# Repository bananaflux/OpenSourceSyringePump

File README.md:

# OpenSourceSyringePump

* Printed circuit board can be easily ordered from OSHPark: [Open Source Syringe Pump PCB](https://oshpark.com/shared_projects/VtseE2Ia)

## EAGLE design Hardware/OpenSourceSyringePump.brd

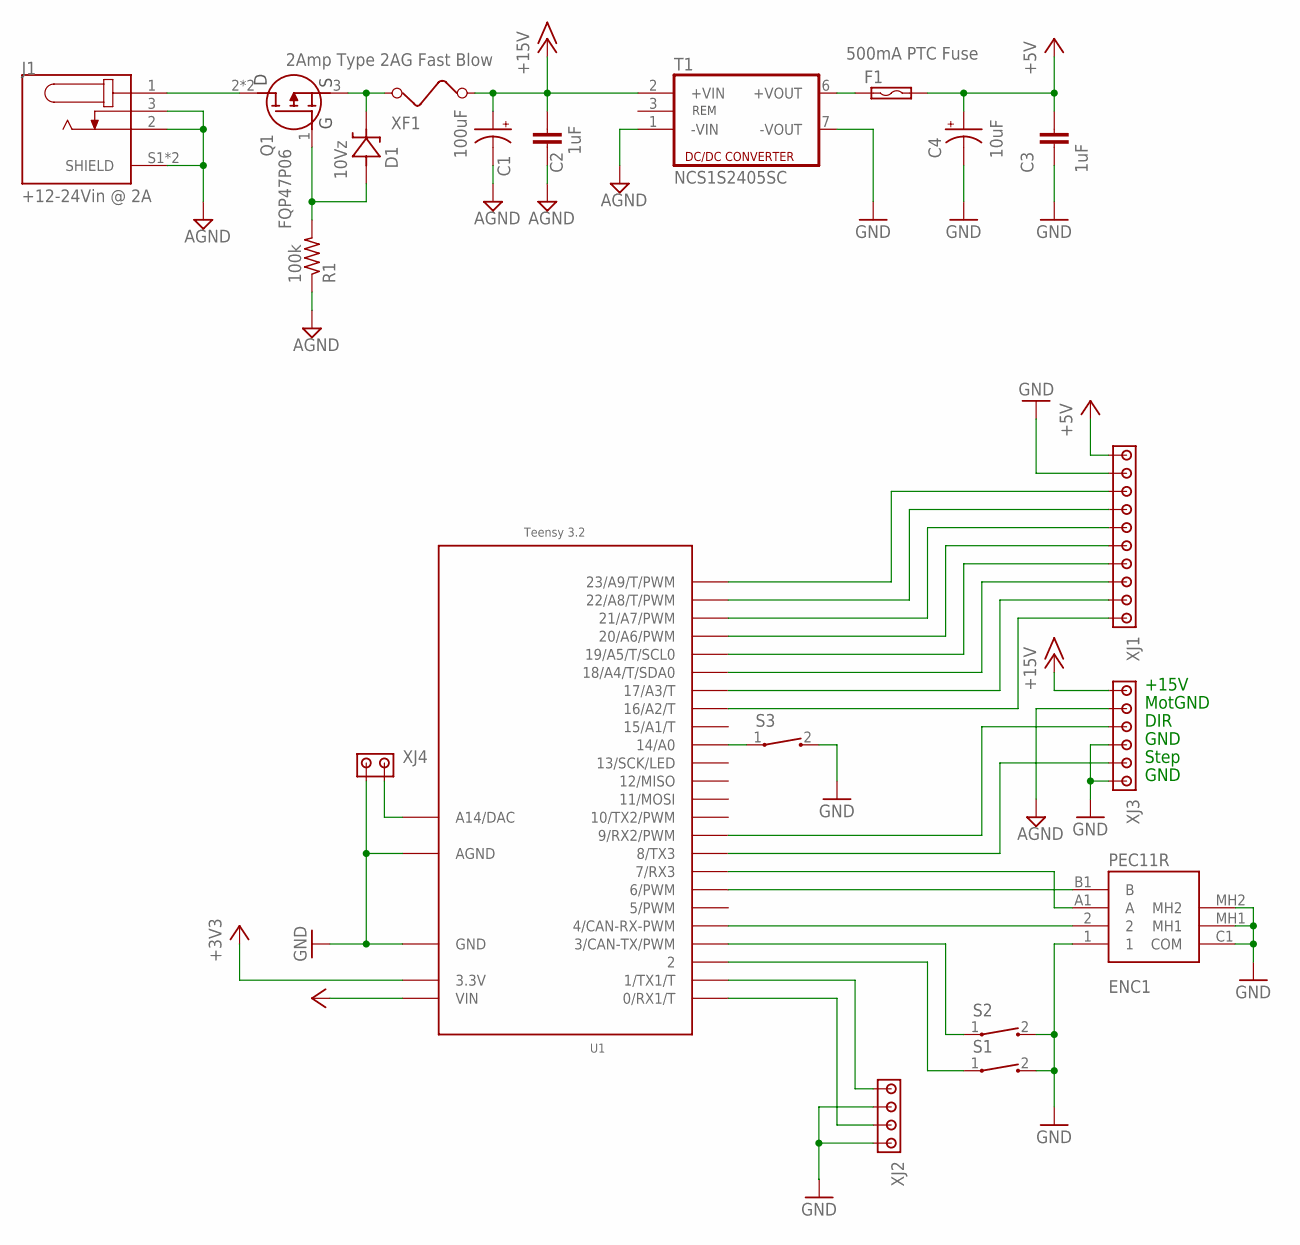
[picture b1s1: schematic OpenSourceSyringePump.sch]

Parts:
C1: 100uF; EEUFR1H101
C2, C3: 1uF; K105Z20Y5VF5TL2
C4: 10uF; TAP106K025SCS
D1: 10Vz; BZX79C10
ENC1: PEC11R; PEC11R4220FS0024
F1: 500mA PTC Fuse; BOURNS-MF-R025
J1: +12-24Vin @ 2A; CUI_PJ-079AH
Q1: FQP47P06
R1: 100k; 0204/7
S1, S2, S3: ALPS-SKRGAFD010
T1: NCS1S2405SC; MURATA-NCS1S2405SC
U1: Teensy 3.2; TEENSY_3.0-3.2&LC_OUTER_ROW
XF1: 2Amp Type 2AG Fast Blow; LITTLEFUSE-02540101Z
XJ1: TE-1-282834-0-DOUBLE
XJ2: TE-282834-4-DOUBLE
XJ3: TE-282834-6-DOUBLE
XJ4: TE-282834-2-DOUBLE

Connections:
+3V3: U1.3.3V
+5V: C3.1, C4.+, F1.2, U1.VIN, XJ1.1, XJ1.P$1 (1)
+15V: C1.+, C2.1, T1.2 (+VIN), XF1.1, XJ3.1, XJ3.P$1 (1)
GND: C3.2, C4.-, ENC1.1, ENC1.C1 (COM), ENC1.MH1, ENC1.MH2, S1.2, S2.2, S3.2, T1.7 (-VOUT), U1.AGND, U1.GND, XJ1.2, XJ1.P$2 (2), XJ2.2, XJ2.4, XJ2.P$2 (2), XJ2.P$4 (4), XJ3.4, XJ3.6, XJ3.P$4 (4), XJ3.P$6 (6), XJ4.1, XJ4.P$1 (1)
MGND: C1.-, C2.2, J1.2, J1.3, J1.S1 (SHIELD), J1.S2 (SHIELD), R1.1, T1.1 (-VIN), XJ3.2, XJ3.P$2 (2)
unnamed: J1.1, Q1.2 (D), Q1.MH (D)
unnamed: D1.A, Q1.1 (G), R1.2
unnamed: F1.1, T1.6 (+VOUT)
unnamed: D1.C, Q1.3 (S), XF1.2
unnamed: ENC1.B1 (B), U1.6 (6/PWM)
unnamed: ENC1.A1 (A), U1.7 (7/RX3)
unnamed: U1.0 (0/RX1/T), XJ2.3, XJ2.P$3 (3)
unnamed: U1.1 (1/TX1/T), XJ2.1, XJ2.P$1 (1)
unnamed: S2.1, U1.3 (3/CAN-TX/PWM)
unnamed: ENC1.2, U1.4 (4/CAN-RX-PWM)
unnamed: S3.1, U1.14/A0
unnamed: U1.8 (8/TX3), XJ3.5, XJ3.P$5 (5)
unnamed: U1.9 (9/RX2/PWM), XJ3.3, XJ3.P$3 (3)
unnamed: U1.16/A2 (16/A2/T), XJ1.10, XJ1.P$10 (10)
unnamed: U1.17/A3 (17/A3/T), XJ1.9, XJ1.P$9 (9)
unnamed: U1.18/A4 (18/A4/T/SDA0), XJ1.8, XJ1.P$8 (8)
unnamed: U1.19/A5 (19/A5/T/SCL0), XJ1.7, XJ1.P$7 (7)
unnamed: U1.20/A6 (20/A6/PWM), XJ1.6, XJ1.P$6 (6)
unnamed: U1.21/A7 (21/A7/PWM), XJ1.5, XJ1.P$5 (5)
unnamed: U1.22/A8 (22/A8/T/PWM), XJ1.4, XJ1.P$4 (4)
unnamed: U1.23/A9 (23/A9/T/PWM), XJ1.3, XJ1.P$3 (3)
unnamed: S1.1, U1.2
unnamed: U1.RESET/DAC (A14/DAC), XJ4.2, XJ4.P$2 (2)

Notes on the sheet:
+15V
MotGND
GND
Step
DIR

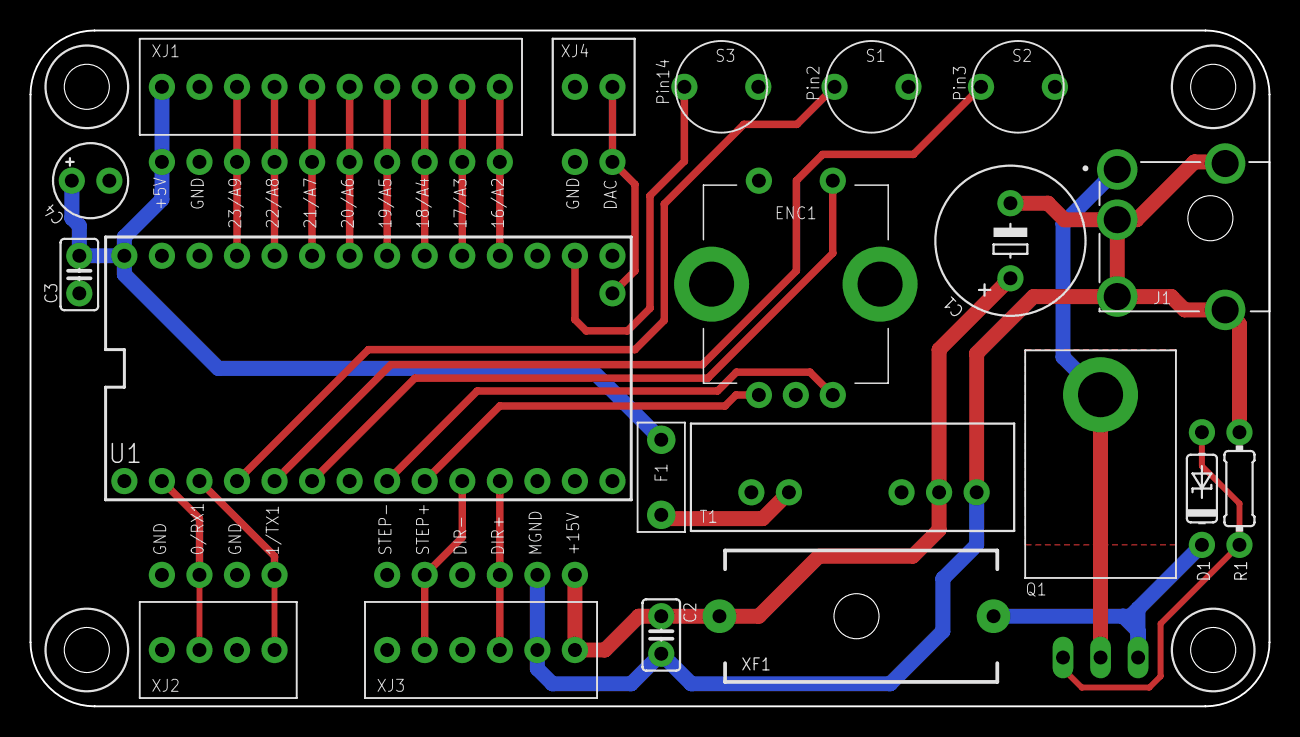
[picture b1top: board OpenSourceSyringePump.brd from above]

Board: 2 copper layers, 83.8 x 45.7 mm, 20 parts (0 on the bottom side), 27 nets.
